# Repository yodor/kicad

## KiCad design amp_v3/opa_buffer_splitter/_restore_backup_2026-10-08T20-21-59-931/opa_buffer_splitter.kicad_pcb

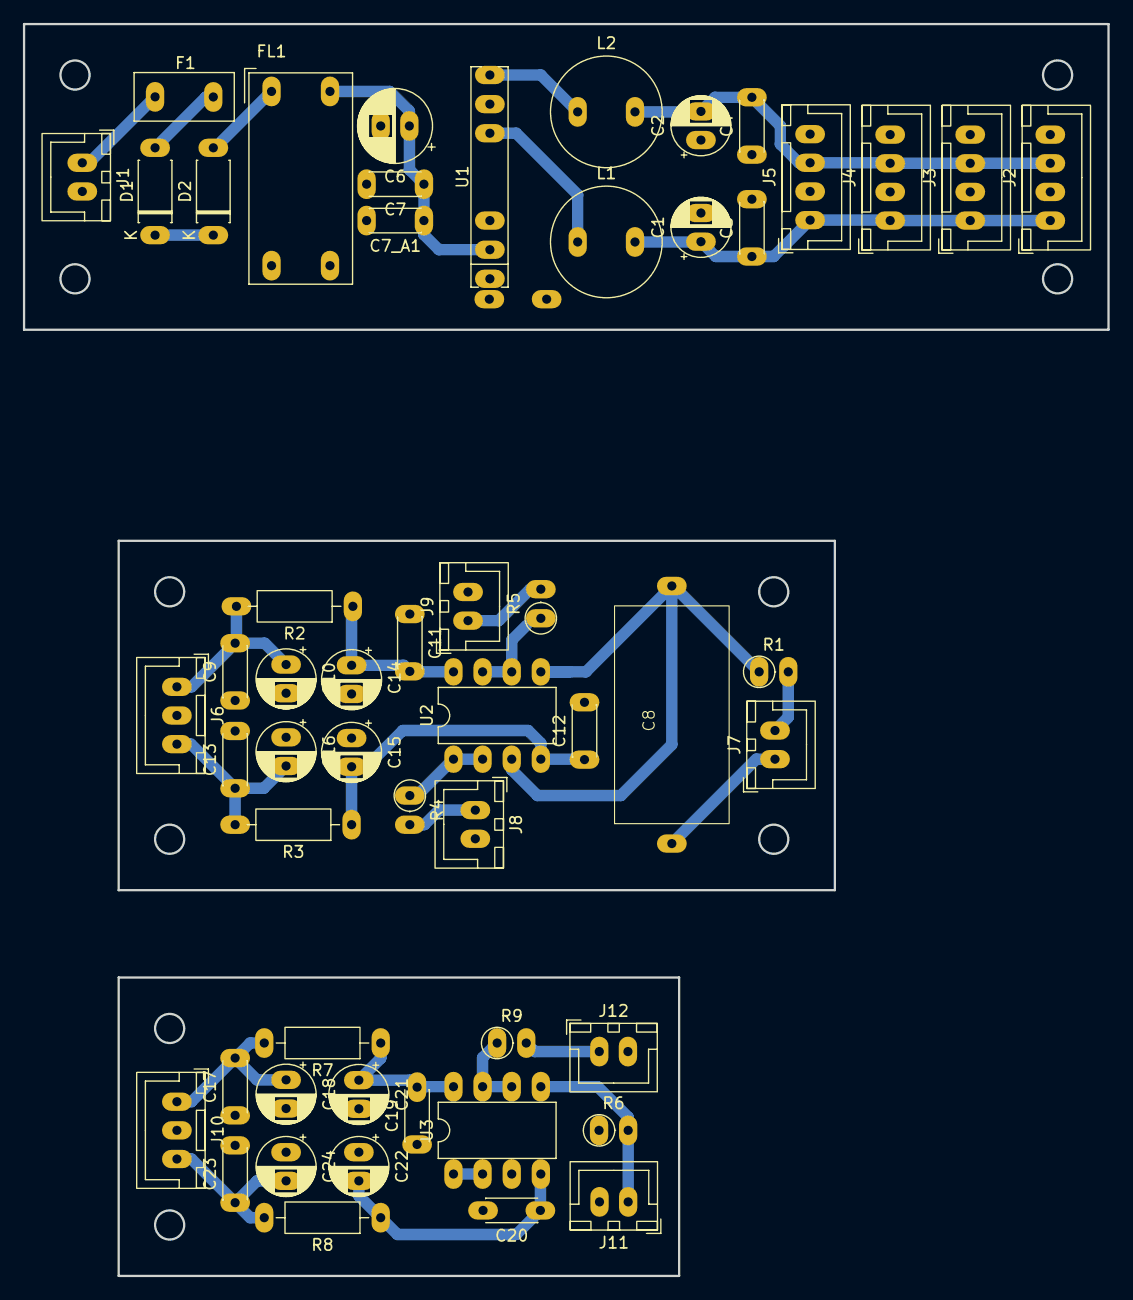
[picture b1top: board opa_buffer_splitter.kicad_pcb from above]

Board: 2 copper layers, 94.6 x 109.2 mm, 55 parts (1 on the bottom side), 32 nets.

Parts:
C1, C2: 10uF; CP_Radial_D5.0mm_P2.50mm
C3, C4: 1uF x7r; C_Disc_D4.3mm_W1.9mm_P5.00mm
C5: 2.2 nF, 2000 V, Y5P; C_Disc_D4.3mm_W1.9mm_P5.00mm
C6: 47uF; CP_Radial_D6.3mm_P2.50mm
C7, C7_A1: 1uF X7R; C_Disc_D4.3mm_W1.9mm_P5.00mm
C8: 1uF PP; JFC
C9, C11, C12, C13, C17, C19, C20, C23: 100nF; C_Disc_D4.3mm_W1.9mm_P5.00mm
C10, C16, C18, C24: 4.7uF; CP_Radial_D5.0mm_P2.50mm
C14, C15, C21, C22: 10uF esr; CP_Radial_D5.0mm_P2.50mm
D1: 1N4007; D_DO-41_SOD81_P7.62mm_Horizontal
D2: 1N5338B; D_DO-41_SOD81_P7.62mm_Horizontal
F1: 1A; Fuse_Littelfuse_395Series
FL1: RN202-0.3-02-12M; Choke_Schaffner_RN202-04-8.8x18.2mm
J1: UHP_PWR; JST_XH_B2B-XH-A_1x02_P2.50mm_Vertical
J2, J3, J4, J5: OP_PWR_OUT; JST_XH_B4B-XH-A_1x04_P2.50mm_Vertical
J6, J10: OP_PWR; JST_XH_B3B-XH-A_1x03_P2.50mm_Vertical
J7, J11: AUDIO_IN; JST_XH_B2B-XH-A_1x02_P2.50mm_Vertical
J8: AOUT_MASTER; JST_XH_B2B-XH-A_1x02_P2.50mm_Vertical
J9: AOUT_VIS; JST_XH_B2B-XH-A_1x02_P2.50mm_Vertical
J12: AUDIO_OUT; JST_XH_B2B-XH-A_1x02_P2.50mm_Vertical
L1, L2: 10uH; L_Radial_D9.5mm_P5.00mm_Fastron_07HVP
R1: 100K; R_Axial_DIN0207_L6.3mm_D2.5mm_P2.54mm_Vertical
R2, R3, R7, R8: 10R; R_Axial_DIN0207_L6.3mm_D2.5mm_P10.16mm_Horizontal
R4, R5, R9: 47R; R_Axial_DIN0207_L6.3mm_D2.5mm_P2.54mm_Vertical
R6: 1M; R_Axial_DIN0207_L6.3mm_D2.5mm_P2.54mm_Vertical
U1: DPB09B-12; SIP-8_19x3mm_P2.54mm
U2, U3: OPA1656; SMDIP-8_W7.62mm

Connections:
/Buffer/+12VA: C17.2, C18.1, J10.1, R7.2
/Buffer/-12VA: C23.1, C24.2, J10.3, R8.2
/Buffer/AUDIO_GND: C17.1, C18.2, C19.1, C20.2, C21.2, C22.1, C23.2, C24.1, J10.2, J11.2, J12.2, R6.1, U3.3 (+)
/Buffer/AUDIO_IN_VACTROL: J11.1, R6.2, U3.5 (+)
/Buffer/AUDIO_OUT_AMP: J12.1, R9.2
/PSU/30V_PRE: C6.1, C7.1, C7_A1.1, FL1.2, U1.2
/PSU/+12VA: C1.1, C3.1, J2.1, J3.1, J4.1, J5.1, L1.2
/PSU/+12V_DC: L1.1, U1.6
/PSU/+36V_UHP: F1.1, J1.1
/PSU/-12VA: C2.2, C4.2, J2.3, J3.3, J4.3, J5.3, L2.2
/PSU/-12V_DC: L2.1, U1.8
/PSU/AUDIO_GND: C1.2, C2.1, C3.2, C4.1, C5.2, J2.2, J2.4, J3.2, J3.4, J4.2, J4.4, J5.2, J5.4, U1.7
/PSU/GND_PRE: C5.1, C6.2, C7.2, C7_A1.2, FL1.4, U1.1
/PSU/GND_UHP: FL1.3, J1.2
/Splitter/+12VA: C9.2, C10.1, J6.1, R2.2
/Splitter/-12VA: C13.1, C16.2, J6.3, R3.2
/Splitter/AUDIO_GND: C9.1, C10.2, C11.1, C12.2, C13.2, C14.2, C15.1, C16.1, J6.2, J7.2, J8.2, J9.2, R1.2
/Splitter/AUDIO_IN: C8.2, R1.1, U2.3 (+), U2.5 (+)
/Splitter/AUDIO_OUT_MASTER: J9.1, R5.2
/Splitter/AUDIO_OUT_VACTROL: J8.1, R4.2
/Splitter/RCA_IN: C8.1, J7.1
unnamed: D1.2 (A), F1.2
unnamed: D1.1 (K), D2.1 (K)
unnamed: D2.2 (A), FL1.1
unnamed: R4.1, U2.1, U2.2 (-)
unnamed: R5.1, U2.6 (-), U2.7
unnamed: C11.2, C14.1, R2.1, U2.8 (V+)
unnamed: C12.1, C15.2, R3.1, U2.4 (V-)
unnamed: U3.1, U3.2 (-)
unnamed: R9.1, U3.6 (-), U3.7
unnamed: C19.2, C21.1, R7.1, U3.8 (V+)
unnamed: C20.1, C22.2, R8.1, U3.4 (V-)

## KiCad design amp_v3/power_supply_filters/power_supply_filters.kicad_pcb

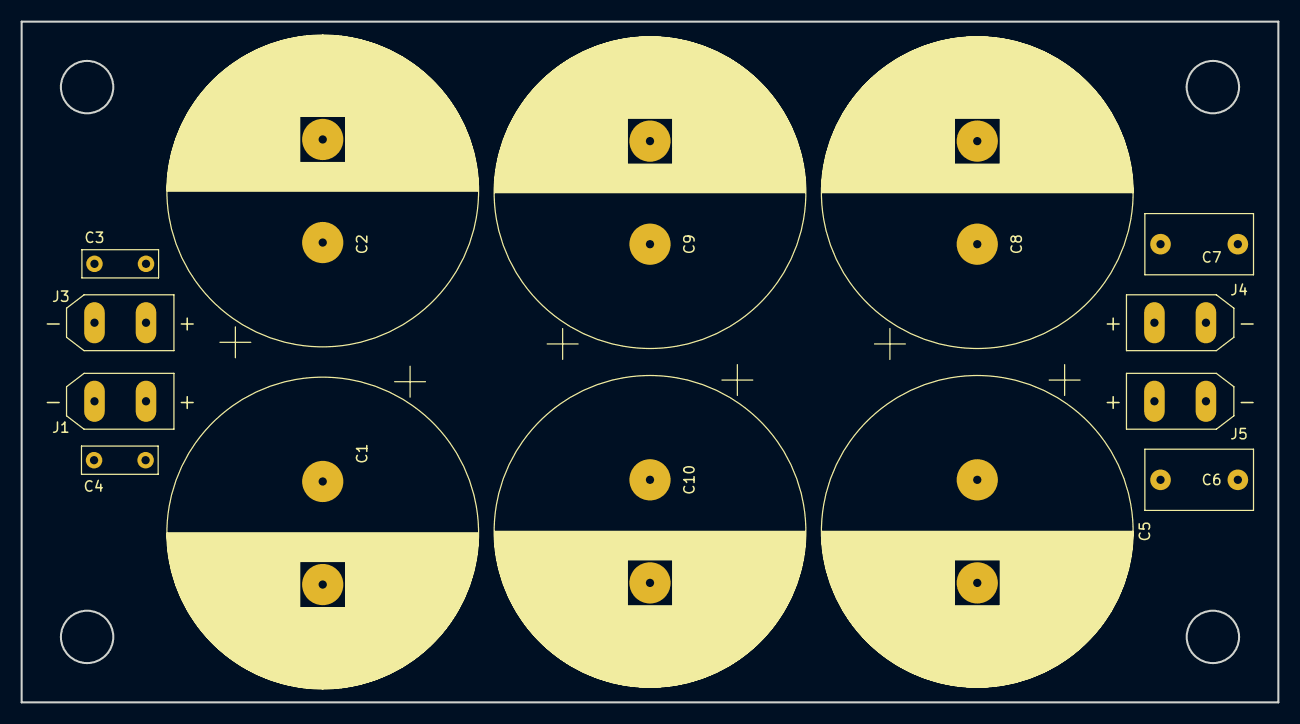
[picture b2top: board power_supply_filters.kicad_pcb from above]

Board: 2 copper layers, 121.9 x 66.0 mm, 15 parts (1 on the bottom side), 3 nets, no tracks yet.

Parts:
C1, C2, C5, C8, C9, C10: 10000uF; CP_Radial_D30.0mm_P10.00mm_SnapIn
C3, C4: 100nF; C_Rect_L7.2mm_W2.5mm_P5.00mm_FKS2_FKP2_MKS2_MKP2
C6, C7: 1uF; C_Rect_L10.3mm_W5.7mm_P7.50mm_MKS4
J1, J3: PWR_IN; AMASS_XT30U-M_1x02_P5.0mm_Vertical
J4, J5: PWR_OUT; AMASS_XT30U-F_1x02_P5.0mm_Vertical
L1: 3.3uH; L_Changjiang_FXL1350

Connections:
GND: C1.2, C2.2, C3.2, C4.2, C5.2, C6.2, C7.2, C8.2, C9.2, C10.2, J1.1, J3.1, J4.1, J5.1
VDD: C5.1, C6.1, C7.1, C8.1, C9.1, C10.1, J4.2, J5.2, L1.2
VDD_IN: C1.1, C2.1, C3.1, C4.1, J1.2, J3.2, L1.1

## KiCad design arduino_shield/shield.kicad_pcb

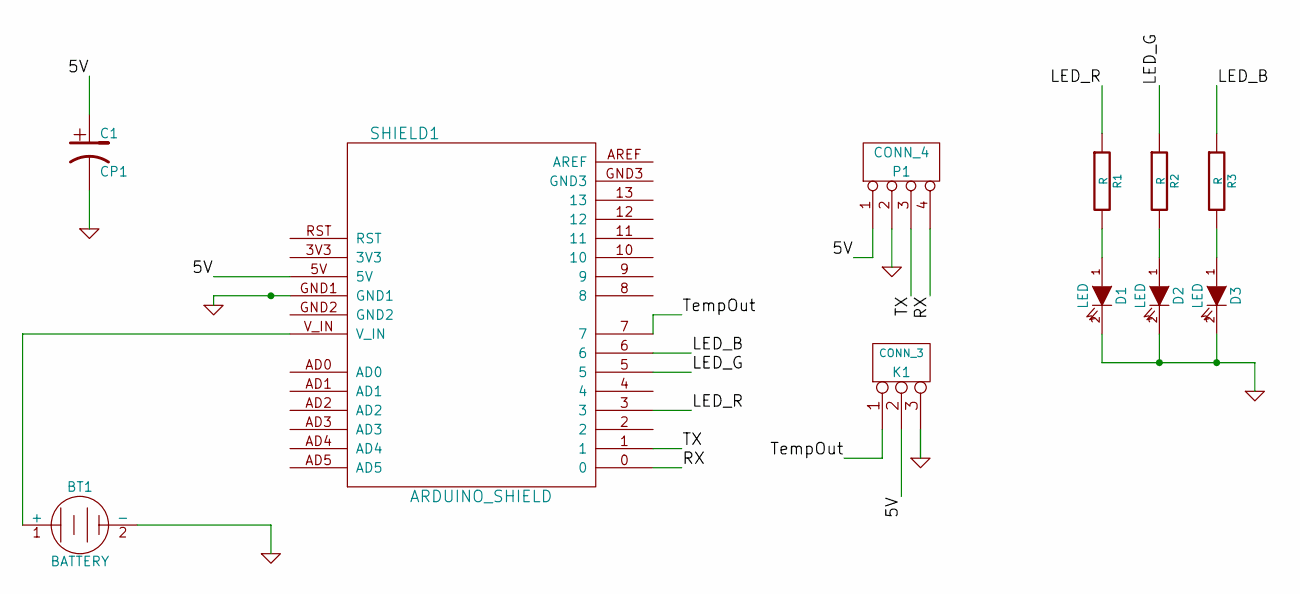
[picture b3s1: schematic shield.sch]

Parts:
BT1: BATTERY
C1: CP1
D1, D2, D3: LED
K1: CONN_3
P1: CONN_4
R1, R2, R3: R
SHIELD1: ARDUINO_SHIELD

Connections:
/5V: C1.1, K1.2 (PM), P1.1, SHIELD1.5V
/LED_B: R3.1, SHIELD1.6
/LED_G: R2.1, SHIELD1.5
/LED_R: R1.1, SHIELD1.3
/RX: P1.4, SHIELD1.0
/TX: P1.3, SHIELD1.1
/TempOut: K1.1, SHIELD1.7
GND: BT1.2 (-), C1.2, D1.2 (K), D2.2 (K), D3.2 (K), K1.3, P1.2, SHIELD1.GND1
unnamed: D2.1 (A), R2.2
unnamed: D3.1 (A), R3.2
unnamed: D1.1 (A), R1.2
unnamed: BT1.1 (+), SHIELD1.V_IN

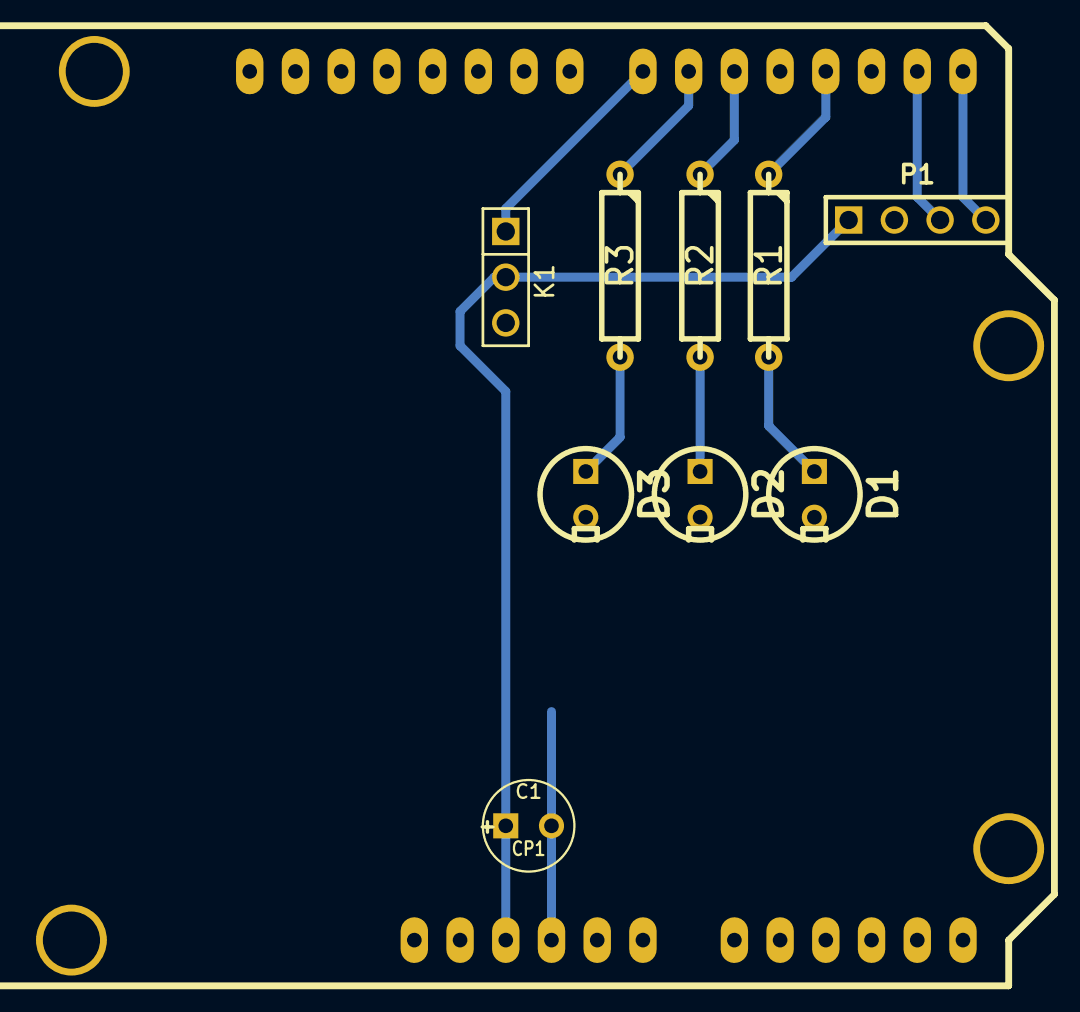
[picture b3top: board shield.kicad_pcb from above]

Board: 2 copper layers, 10 parts (0 on the bottom side), 11 nets.
